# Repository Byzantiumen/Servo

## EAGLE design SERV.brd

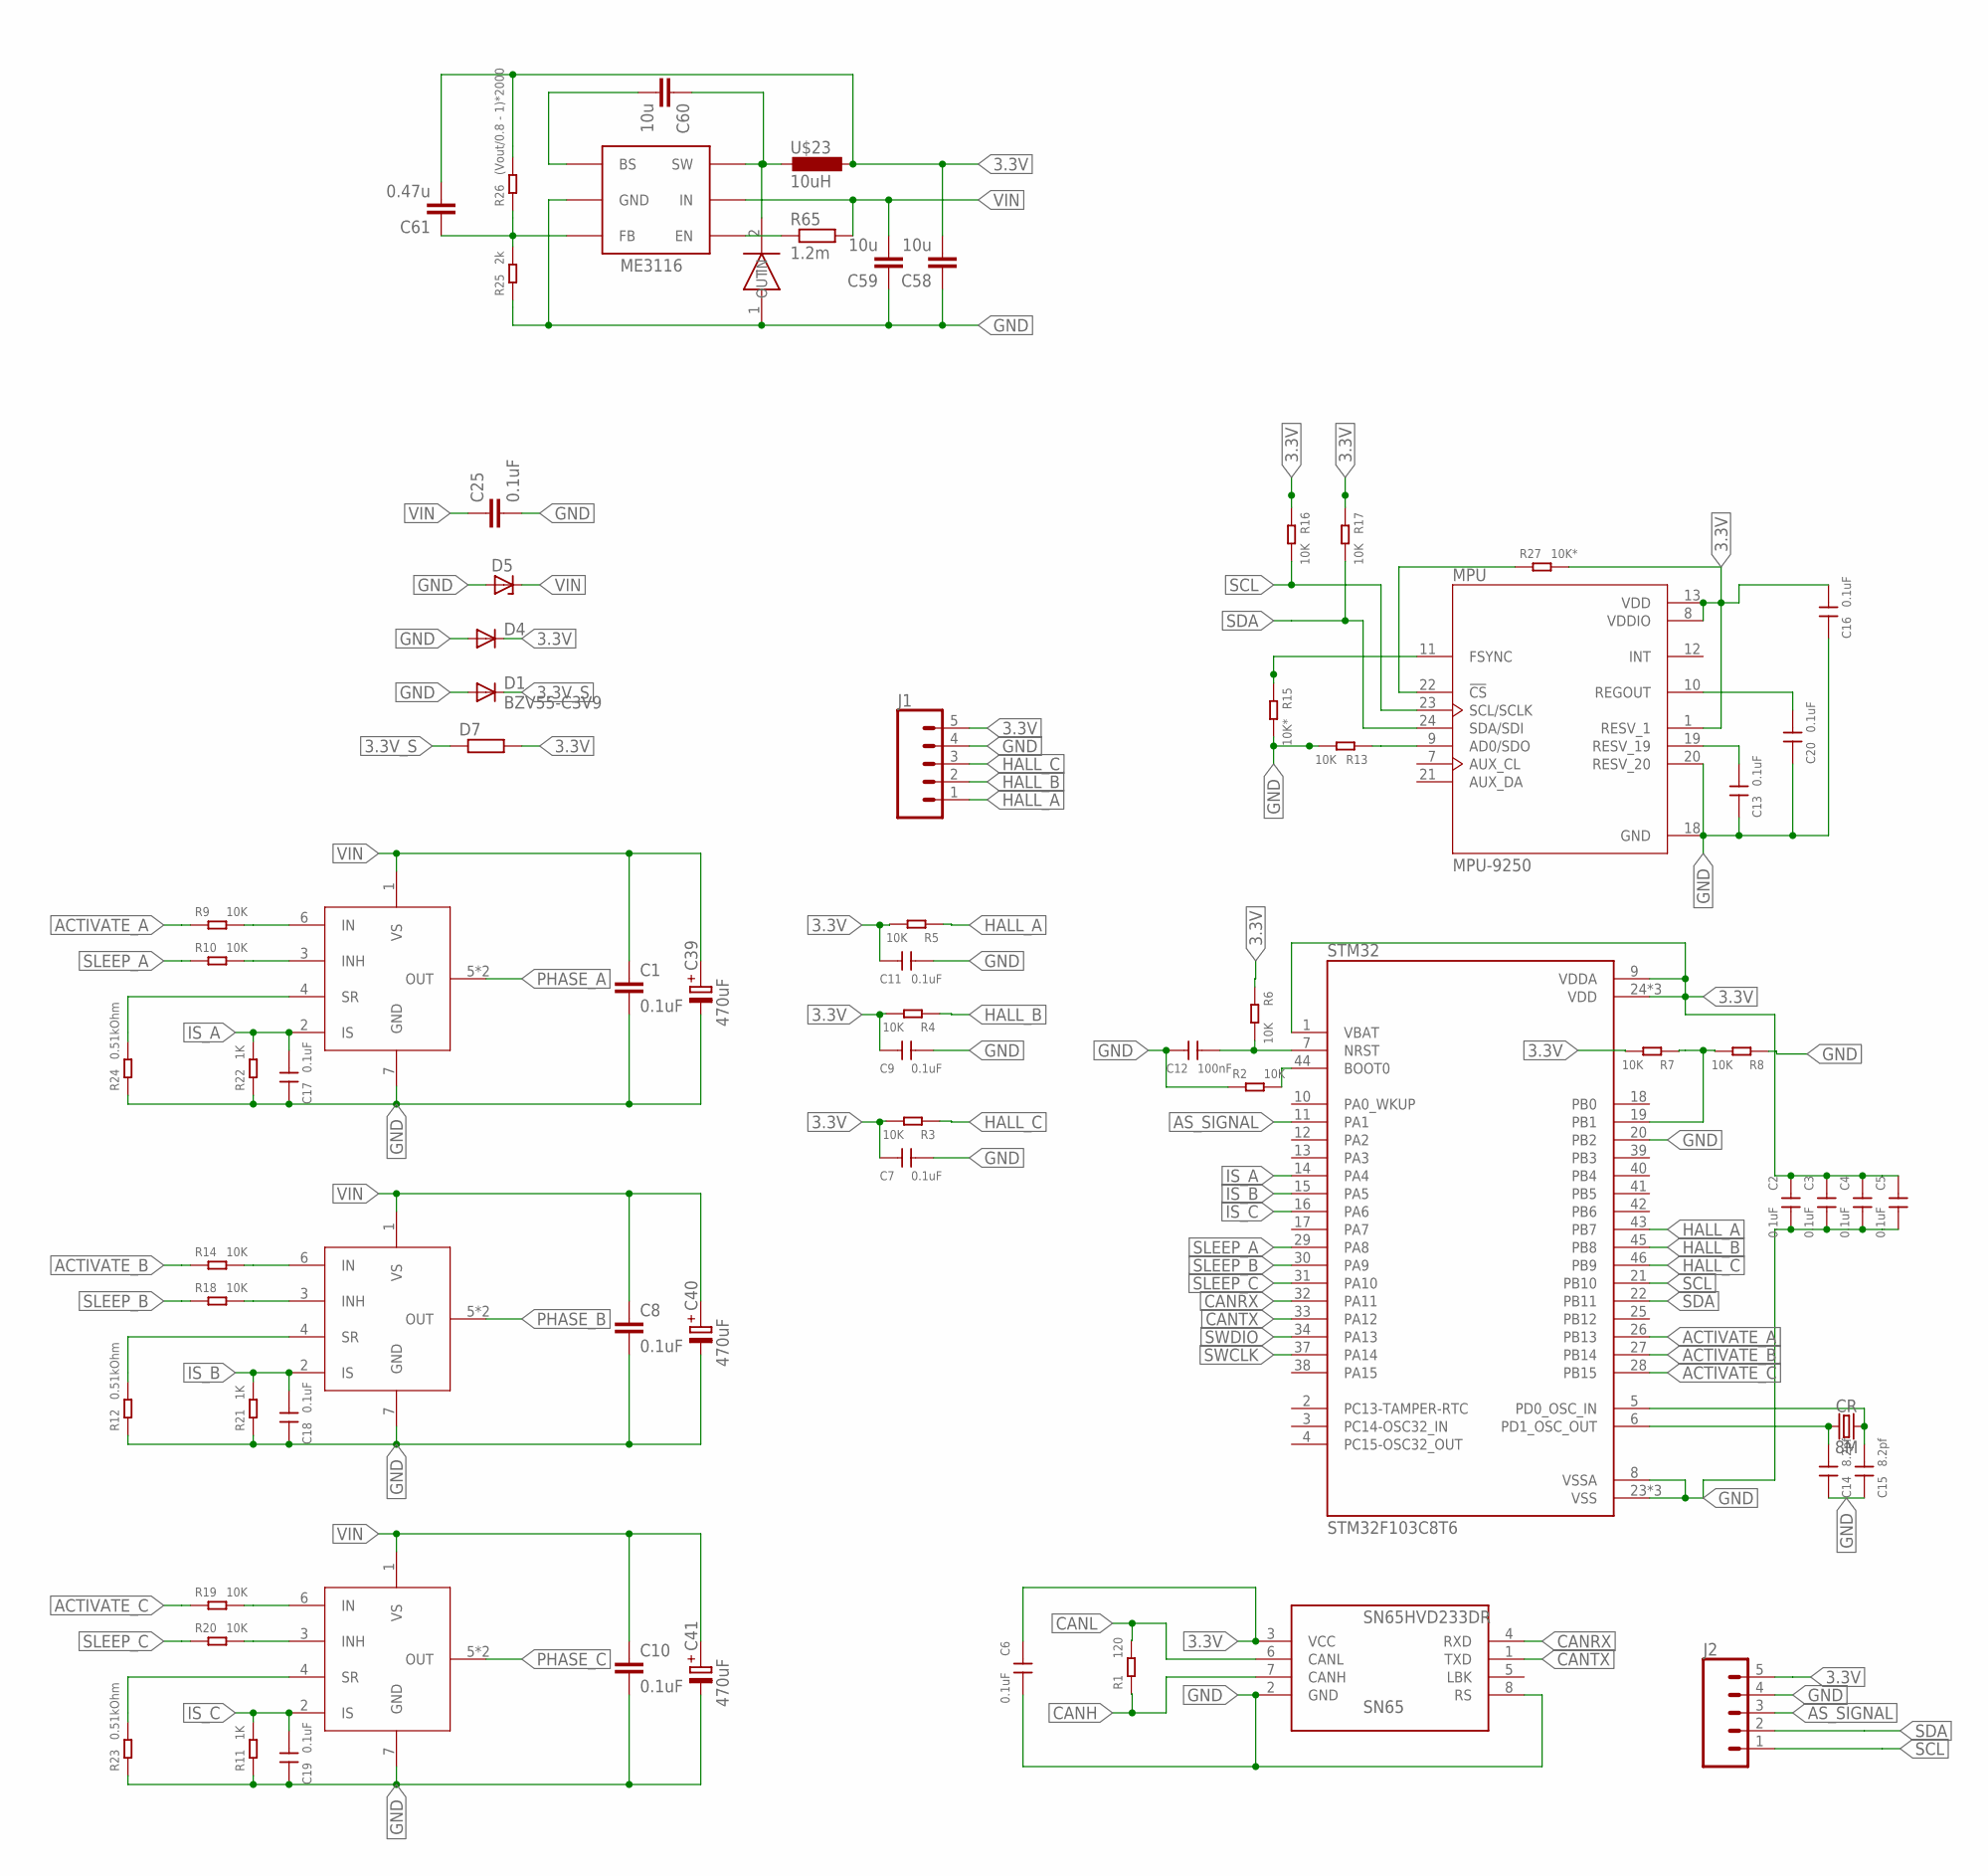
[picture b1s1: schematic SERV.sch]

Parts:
BTN_A: BTN7960B; DPAK127P1500X440-8N
BTN_B: BTN7960B; DPAK127P1500X440-8N
BTN_C: BTN7960B; DPAK127P1500X440-8N
C1, C8, C10, C25: 0.1uF; C1206
C2, C3, C4, C5, C6, C7, C9, C11, C13, C16, C17, C18, C19, C20: 0.1uF; 0603
C12: 100nF; 0603
C14, C15: 8.2pf; 0603
C39, C40, C41: 470uF; TE-D-7343
C58, C59, C60: 10u; C0805
C61: 0.47u; C0805
CR: 8M; CRYSTAL-SMD-3.2X2.5MM
D1: BZV55-C3V9; MINIMELF
D4: DIODE-MINIMELF; MINIMELF
D5: ZENER-DIODESMB; SMB
D7: R-EU_R0805W; R0805W
J1, J2: CONN_05; 1X05
ME311: ME3116; SOT-23-6
MPU: MPU-9250; QFN40P300X300X105-24N
R1: 120; 0603
R2, R3, R4, R5, R6, R7, R8, R9, R10, R13, R14, R16, R17, R18, R19, R20: 10K; 0603
R11, R21, R22: 1K; 0603
R12, R23, R24: 0.51kOhm; 0603
R15, R27: 10K*; 0603
R25: 2k; 0603
R26: (Vout/0.8 - 1)*2000; 0603
R65: 1.2m; R0603
SN65: SN65HVD233DR; SOIC8
STM32: STM32F103C8T6; QFP50P900X900X160-48N
U$1: SMA-SS34
U$23: 10uH; CD43

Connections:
3.3V: C2.1, C3.1, C4.1, C5.1, C6.1, C7.1, C9.1, C11.1, C16.2, C58.2, C61.2, D4.C, D7.2, J1.5, J2.5, MPU.1 (RESV_1), MPU.8 (VDDIO), MPU.13 (VDD), R3.2, R4.2, R5.2, R6.1, R7.2, R16.1, R17.1, R26.2, R27.2, SN65.3 (VCC), STM32.1 (VBAT), STM32.9 (VDDA), STM32.24 (VDD), STM32.36 (VDD), STM32.48 (VDD), U$23.P$1 (1)
3.3V_S: D1.C, D7.1
ACTIVATE_A: R9.1, STM32.26 (PB13)
ACTIVATE_B: R14.1, STM32.27 (PB14)
ACTIVATE_C: R19.1, STM32.28 (PB15)
AS_SIGNAL: J2.3, STM32.11 (PA1)
CANH: R1.1, SN65.7 (CANH)
CANL: R1.2, SN65.6 (CANL)
CANRX: SN65.4 (RXD), STM32.32 (PA11)
CANTX: SN65.1 (TXD), STM32.33 (PA12)
GND: BTN_A.7 (GND), BTN_B.7 (GND), BTN_C.7 (GND), C1.2, C2.2, C3.2, C4.2, C5.2, C6.2, C7.2, C8.2, C9.2, C10.2, C11.2, C12.1, C13.1, C14.1, C15.1, C16.1, C17.1, C18.1, C19.1, C20.1, C25.2, C39.-, C40.-, C41.-, C58.1, C59.1, D1.A, D4.A, D5.A, J1.4, J2.4, ME311.2 (GND), MPU.18 (GND), MPU.20 (RESV_20), MPU.25, R2.1, R8.1, R11.1, R12.1, R13.2, R15.2, R21.1, R22.1, R23.1, R24.1, R25.1, SN65.2 (GND), SN65.8 (RS), STM32.8 (VSSA), STM32.20 (PB2), STM32.23 (VSS), STM32.35 (VSS), STM32.47 (VSS), U$1.1 (IN)
HALL_A: J1.1, R5.1, STM32.43 (PB7)
HALL_B: J1.2, R4.1, STM32.45 (PB8)
HALL_C: J1.3, R3.1, STM32.46 (PB9)
IS_A: BTN_C.2 (IS), C17.2, R22.2, STM32.14 (PA4)
IS_B: BTN_B.2 (IS), C18.2, R21.2, STM32.15 (PA5)
IS_C: BTN_A.2 (IS), C19.2, R11.2, STM32.16 (PA6)
unnamed: MPU.9 (AD0/SDO), R13.1
unnamed: R2.2, STM32.44 (BOOT0)
unnamed: C20.2, MPU.10 (REGOUT)
unnamed: MPU.22 (!CS), R27.1
unnamed: BTN_C.4 (SR), R24.2
unnamed: BTN_B.6 (IN), R14.2
unnamed: BTN_B.4 (SR), R12.2
unnamed: BTN_A.6 (IN), R19.2
unnamed: BTN_A.4 (SR), R23.2
unnamed: BTN_B.3 (INH), R18.2
unnamed: BTN_A.3 (INH), R20.2
unnamed: C13.2, MPU.19 (RESV_19)
unnamed: MPU.11 (FSYNC), R15.1
unnamed: C15.2, CR.3 (2), STM32.5 (PD0_OSC_IN)
unnamed: C14.2, CR.1, STM32.6 (PD1_OSC_OUT)
unnamed: C12.2, R6.2, STM32.7 (NRST)
unnamed: BTN_C.6 (IN), R9.2
unnamed: BTN_C.3 (INH), R10.2
unnamed: R7.1, R8.2, STM32.19 (PB1)
unnamed: C60.2, ME311.1 (BS)
unnamed: C61.1, ME311.3 (FB), R25.2, R26.1
unnamed: ME311.4 (EN), R65.1
unnamed: C60.1, ME311.6 (SW), U$1.2 (OUT), U$23.P$2 (2)
PHASE_A: BTN_C.5 (OUT), BTN_C.8 (OUT)
PHASE_B: BTN_B.5 (OUT), BTN_B.8 (OUT)
PHASE_C: BTN_A.5 (OUT), BTN_A.8 (OUT)
SCL: J2.1, MPU.23 (SCL/SCLK), R16.2, STM32.21 (PB10)
SDA: J2.2, MPU.24 (SDA/SDI), R17.2, STM32.22 (PB11)
SLEEP_A: R10.1, STM32.29 (PA8)
SLEEP_B: R18.1, STM32.30 (PA9)
SLEEP_C: R20.1, STM32.31 (PA10)
SWCLK: STM32.37 (PA14)
SWDIO: STM32.34 (PA13)
VIN: BTN_A.1 (VS), BTN_B.1 (VS), BTN_C.1 (VS), C1.1, C8.1, C10.1, C25.1, C39.+, C40.+, C41.+, C59.2, D5.C, ME311.5 (IN), R65.2

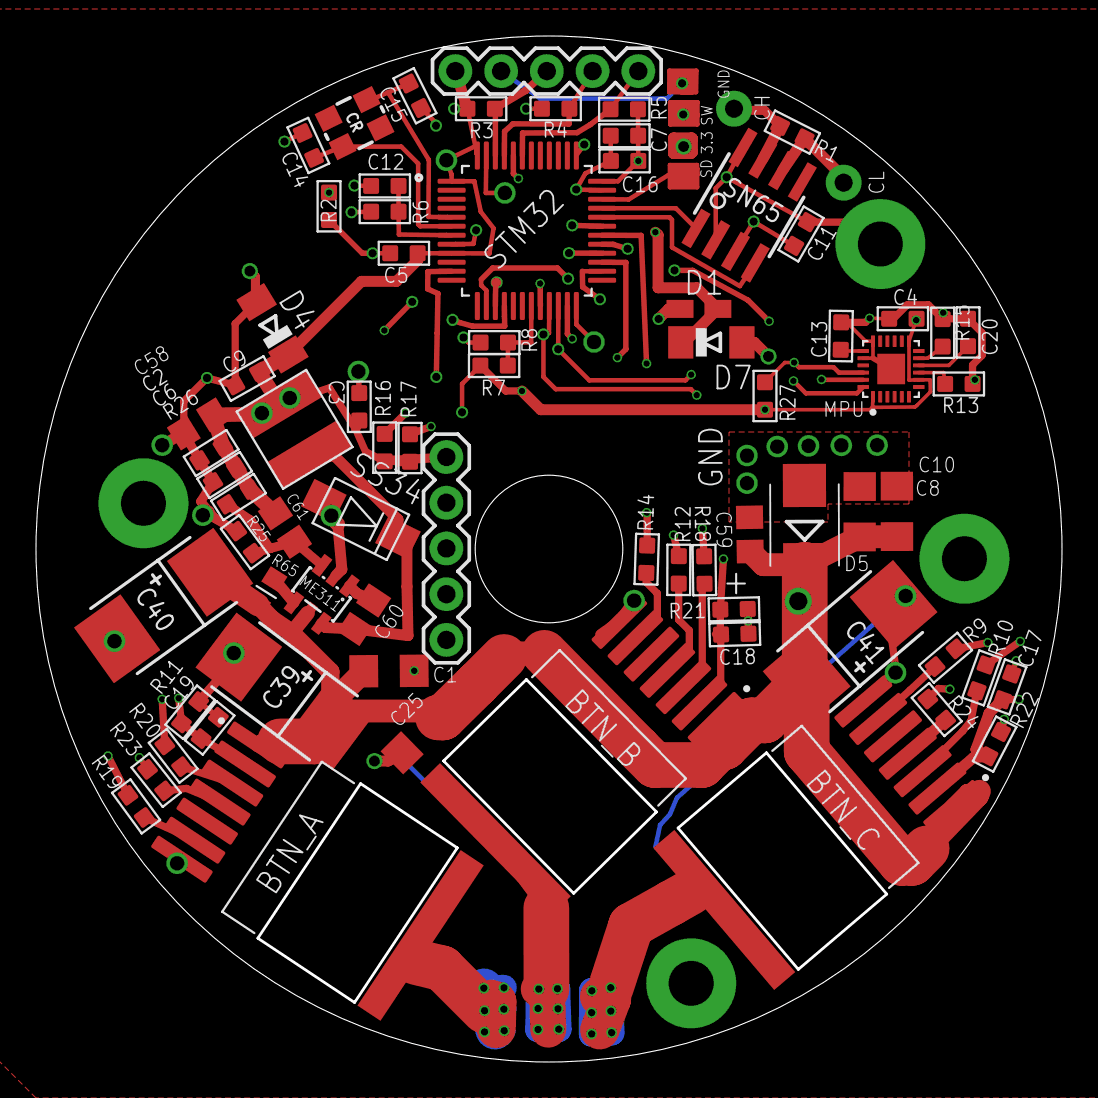
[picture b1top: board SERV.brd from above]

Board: 4 copper layers, 56.8 x 56.8 mm, 72 parts (0 on the bottom side), 49 nets.

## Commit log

2020-07-22 Bord
2020-07-22 Proverca
2020-07-25 Исправлено
2020-07-31 fixed

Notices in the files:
parts and their libraries:
SparkFun-Connectors: Licensing: Creative Commons ShareAlike 4.0 International - https://creativecommons.org/licenses/by-sa/4.0
cap-pan40: Copyright (C) 2004, Bob Starr
